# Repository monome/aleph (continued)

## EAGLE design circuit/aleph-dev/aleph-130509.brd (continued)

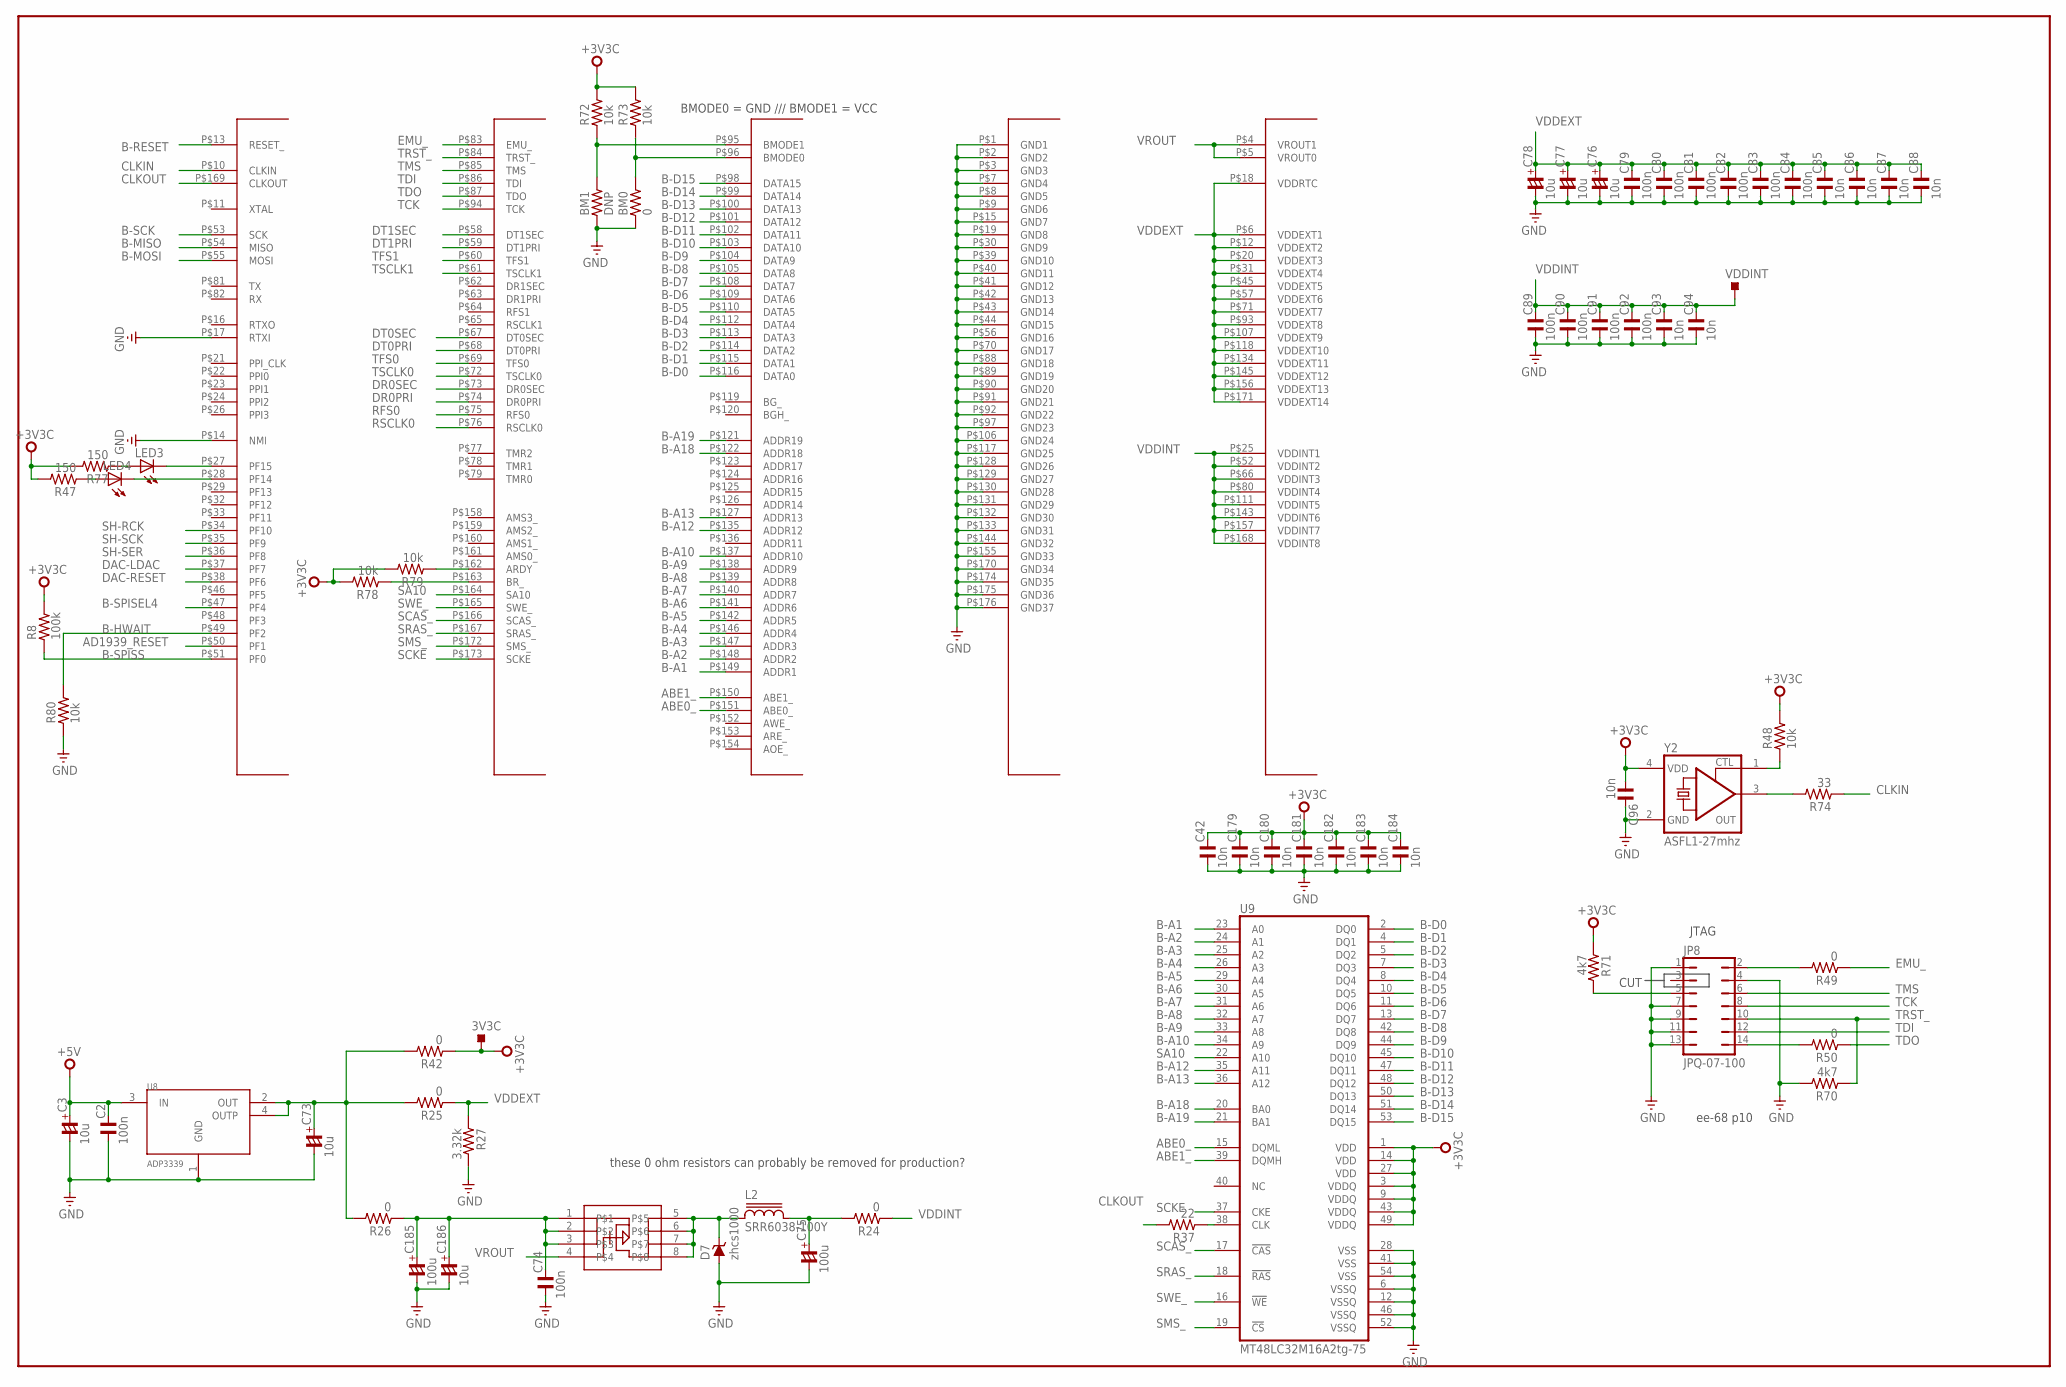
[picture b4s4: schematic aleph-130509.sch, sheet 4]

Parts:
3V3C: TPS-SMD-15R; SMD-15R
BM0: 0; R0603
BM1: DNP; R0603
C2, C74: 100n; C1206
C3, C73, C76, C77, C78, C186: 10u; C1206/T
C42, C85, C86, C87, C88, C93, C94, C96, C179, C180, C181, C182, C183, C184: 10n; C0603
C75, C185: 100u; C1210/T
C79, C80, C81, C82, C83, C84, C89, C90, C91, C92: 100n; C0603
D7: zhcs1000; SOT23
DSP1: BF533; LQFP176
JP8: JPQ-07-100; JPQ-07
L2: SRR6038-100Y; SRR6038
LED3, LED4: LEDCHIPLED_0805; CHIPLED_0805
R8: 100k; R0603
R24, R25, R26, R42, R49, R50: 0; R0603
R27: 3.32k; R0603
R37: 22; R0603
R47, R77: 150; R0603
R48, R72, R73, R78, R79, R80: 10k; R0603
R70, R71: 4k7; R0603
R74: 33; R0603
U8: ADP3339; SOT223
U9: MT48LC32M16A2tg-75; TSOP54
U18: FDS9431A; SO08
VDDINT: TPS-SMD-10R; SMD-10R
Y2: ASFL1-27mhz; ASFL1

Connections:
+3V3C: 3V3C.TP, C42.2, C96.1, C179.2, C180.2, C181.2, C182.2, C183.2, C184.2, R8.2, R42.1, R47.2, R48.2, R71.1, R72.2, R73.2, R77.2, R78.2, R79.2, U9.1 (VDD), U9.3 (VDDQ), U9.9 (VDDQ), U9.14 (VDD), U9.27 (VDD), U9.43 (VDDQ), U9.49 (VDDQ), Y2.4 (VDD); also elsewhere on the board
+5V: C2.2, C3.+, U8.3 (IN); also elsewhere on the board
ABE0_: DSP1.P$151 (ABE0_), U9.15 (DQML)
ABE1_: DSP1.P$150 (ABE1_), U9.39 (DQMH)
AD1939_RESET: DSP1.P$50 (PF1); also elsewhere on the board
B-A1: DSP1.P$149 (ADDR1), U9.23 (A0)
B-A2: DSP1.P$148 (ADDR2), U9.24 (A1)
B-A3: DSP1.P$147 (ADDR3), U9.25 (A2)
B-A4: DSP1.P$146 (ADDR4), U9.26 (A3)
B-A5: DSP1.P$142 (ADDR5), U9.29 (A4)
B-A6: DSP1.P$141 (ADDR6), U9.30 (A5)
B-A7: DSP1.P$140 (ADDR7), U9.31 (A6)
B-A8: DSP1.P$139 (ADDR8), U9.32 (A7)
B-A9: DSP1.P$138 (ADDR9), U9.33 (A8)
B-A10: DSP1.P$137 (ADDR10), U9.34 (A9)
B-A12: DSP1.P$135 (ADDR12), U9.35 (A11)
B-A13: DSP1.P$127 (ADDR13), U9.36 (A12)
B-A18: DSP1.P$122 (ADDR18), U9.20 (BA0)
B-A19: DSP1.P$121 (ADDR19), U9.21 (BA1)
B-D0: DSP1.P$116 (DATA0), U9.2 (DQ0)
B-D1: DSP1.P$115 (DATA1), U9.4 (DQ1)
B-D2: DSP1.P$114 (DATA2), U9.5 (DQ2)
B-D3: DSP1.P$113 (DATA3), U9.7 (DQ3)
B-D4: DSP1.P$112 (DATA4), U9.8 (DQ4)
B-D5: DSP1.P$110 (DATA5), U9.10 (DQ5)
B-D6: DSP1.P$109 (DATA6), U9.11 (DQ6)
B-D7: DSP1.P$108 (DATA7), U9.13 (DQ7)
B-D8: DSP1.P$105 (DATA8), U9.42 (DQ8)
B-D9: DSP1.P$104 (DATA9), U9.44 (DQ9)
B-D10: DSP1.P$103 (DATA10), U9.45 (DQ10)
B-D11: DSP1.P$102 (DATA11), U9.47 (DQ11)
B-D12: DSP1.P$101 (DATA12), U9.48 (DQ12)
B-D13: DSP1.P$100 (DATA13), U9.50 (DQ13)
B-D14: DSP1.P$99 (DATA14), U9.51 (DQ14)
B-D15: DSP1.P$98 (DATA15), U9.53 (DQ15)
B-HWAIT: DSP1.P$49 (PF2), R80.2; also elsewhere on the board
B-MISO: DSP1.P$54 (MISO); also elsewhere on the board
B-MOSI: DSP1.P$55 (MOSI); also elsewhere on the board
B-RESET: DSP1.P$13 (RESET_); also elsewhere on the board
B-SCK: DSP1.P$53 (SCK); also elsewhere on the board
B-SPISEL4: DSP1.P$47 (PF4)
B-SPISS: DSP1.P$51 (PF0), R8.1; also elsewhere on the board
BMODE0: BM0.2, DSP1.P$96 (BMODE0), R73.1
BMODE1: BM1.2, DSP1.P$95 (BMODE1), R72.1
CLKIN: DSP1.P$10 (CLKIN), R74.1
CLKOUT: DSP1.P$169 (CLKOUT), R37.2
DAC-LDAC: DSP1.P$37 (PF7); also elsewhere on the board
DAC-RESET: DSP1.P$38 (PF6); also elsewhere on the board
DR0PRI: DSP1.P$74 (DR0PRI); also elsewhere on the board
DR0SEC: DSP1.P$73 (DR0SEC); also elsewhere on the board
DT0PRI: DSP1.P$68 (DT0PRI); also elsewhere on the board
DT0SEC: DSP1.P$67 (DT0SEC); also elsewhere on the board
DT1PRI: DSP1.P$59 (DT1PRI)
DT1SEC: DSP1.P$58 (DT1SEC); also elsewhere on the board
EMU_: DSP1.P$83 (EMU_), R49.1
GND: BM0.1, BM1.1, C2.1, C3.-, C42.1, C73.-, C74.1, C75.-, C76.-, C77.-, C78.-, C79.1, C80.1, C81.1, C82.1, C83.1, C84.1, C85.1, C86.1, C87.1, C88.1, C89.1, C90.1, C91.1, C92.1, C93.1, C94.1, C96.2, C179.1, C180.1, C181.1, C182.1, C183.1, C184.1, C185.-, C186.-, D7.1 (A), DSP1.P$1 (GND1), DSP1.P$2 (GND2), DSP1.P$3 (GND3), DSP1.P$7 (GND4), DSP1.P$8 (GND5), DSP1.P$9 (GND6), DSP1.P$14 (NMI), DSP1.P$15 (GND7), DSP1.P$17 (RTXI), DSP1.P$19 (GND8), DSP1.P$30 (GND9), DSP1.P$39 (GND10), DSP1.P$40 (GND11), DSP1.P$41 (GND12), DSP1.P$42 (GND13), DSP1.P$43 (GND14), DSP1.P$44 (GND15), DSP1.P$56 (GND16), DSP1.P$70 (GND17), DSP1.P$88 (GND18), DSP1.P$89 (GND19), DSP1.P$90 (GND20), DSP1.P$91 (GND21), DSP1.P$92 (GND22), DSP1.P$97 (GND23), DSP1.P$106 (GND24), DSP1.P$117 (GND25), DSP1.P$128 (GND26), DSP1.P$129 (GND27), DSP1.P$130 (GND28), DSP1.P$131 (GND29), DSP1.P$132 (GND30), DSP1.P$133 (GND31), DSP1.P$144 (GND32), DSP1.P$155 (GND33), DSP1.P$170 (GND34), DSP1.P$174 (GND35), DSP1.P$175 (GND36), DSP1.P$176 (GND37), JP8.1, JP8.4, JP8.7, JP8.9, JP8.11, JP8.13, R27.2, R70.2, R80.1, U8.1 (GND), U9.6 (VSSQ), U9.12 (VSSQ), U9.28 (VSS), U9.41 (VSS), U9.46 (VSSQ), U9.52 (VSSQ), U9.54 (VSS), Y2.2 (GND); also elsewhere on the board
unnamed: C73.+, R25.2, R26.2, R42.2, U8.2 (OUT), U8.4 (OUTP)
unnamed: C74.2, C185.+, C186.+, R26.1, U18.1, U18.2, U18.3
unnamed: D7.3 (C), L2.1, U18.5, U18.6, U18.7, U18.8
unnamed: C75.+, L2.2, R24.2
unnamed: R37.1, U9.38 (CLK)
unnamed: R48.1, Y2.1 (CTL)
unnamed: JP8.2, R49.2
unnamed: JP8.5, R71.2
unnamed: DSP1.P$163 (BR_), R78.1
unnamed: JP8.14, R50.2
unnamed: DSP1.P$162 (ARDY), R79.1
unnamed: R74.2, Y2.3 (OUT)
unnamed: DSP1.P$27 (PF15), LED3.C
unnamed: DSP1.P$28 (PF14), LED4.C
unnamed: LED3.A, R77.1
unnamed: LED4.A, R47.1
RFS0: DSP1.P$75 (RFS0); also elsewhere on the board
RSCLK0: DSP1.P$76 (RSCLK0); also elsewhere on the board
SA10: DSP1.P$164 (SA10), U9.22 (A10)
SCAS_: DSP1.P$166 (SCAS_), U9.17 (!CAS!)
SCKE: DSP1.P$173 (SCKE), U9.37 (CKE)
SH-RCK: DSP1.P$34 (PF10)
SH-SCK: DSP1.P$35 (PF9)
SH-SER: DSP1.P$36 (PF8)
SMS_: DSP1.P$172 (SMS_), U9.19 (!CS!)
SRAS_: DSP1.P$167 (SRAS_), U9.18 (!RAS!)
SWE_: DSP1.P$165 (SWE_), U9.16 (!WE!)
TCK: DSP1.P$94 (TCK), JP8.8
TDI: DSP1.P$86 (TDI), JP8.12
TDO: DSP1.P$87 (TDO), R50.1
TFS0: DSP1.P$69 (TFS0); also elsewhere on the board
TFS1: DSP1.P$60 (TFS1); also elsewhere on the board
TMS: DSP1.P$85 (TMS), JP8.6
TRST_: DSP1.P$84 (TRST_), JP8.10, R70.1
TSCLK0: DSP1.P$72 (TSCLK0); also elsewhere on the board
TSCLK1: DSP1.P$61 (TSCLK1); also elsewhere on the board
VDDEXT: C76.+, C77.+, C78.+, C79.2, C80.2, C81.2, C82.2, C83.2, C84.2, C85.2, C86.2, C87.2, C88.2, DSP1.P$6 (VDDEXT1), DSP1.P$12 (VDDEXT2), DSP1.P$18 (VDDRTC), DSP1.P$20 (VDDEXT3), DSP1.P$31 (VDDEXT4), DSP1.P$45 (VDDEXT5), DSP1.P$57 (VDDEXT6), DSP1.P$71 (VDDEXT7), DSP1.P$93 (VDDEXT8), DSP1.P$107 (VDDEXT9), DSP1.P$118 (VDDEXT10), DSP1.P$134 (VDDEXT11), DSP1.P$145 (VDDEXT12), DSP1.P$156 (VDDEXT13), DSP1.P$171 (VDDEXT14), R25.1, R27.1
VDDINT: C89.2, C90.2, C91.2, C92.2, C93.2, C94.2, DSP1.P$25 (VDDINT1), DSP1.P$52 (VDDINT2), DSP1.P$66 (VDDINT3), DSP1.P$80 (VDDINT4), DSP1.P$111 (VDDINT5), DSP1.P$143 (VDDINT6), DSP1.P$157 (VDDINT7), DSP1.P$168 (VDDINT8), R24.1, VDDINT.TP
VROUT: DSP1.P$4 (VROUT1), DSP1.P$5 (VROUT0), U18.4

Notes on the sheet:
these 0 ohm resistors can probably be removed for production?
ee-68 p10
CUT
JTAG
BMODE0 = GND /// BMODE1 = VCC

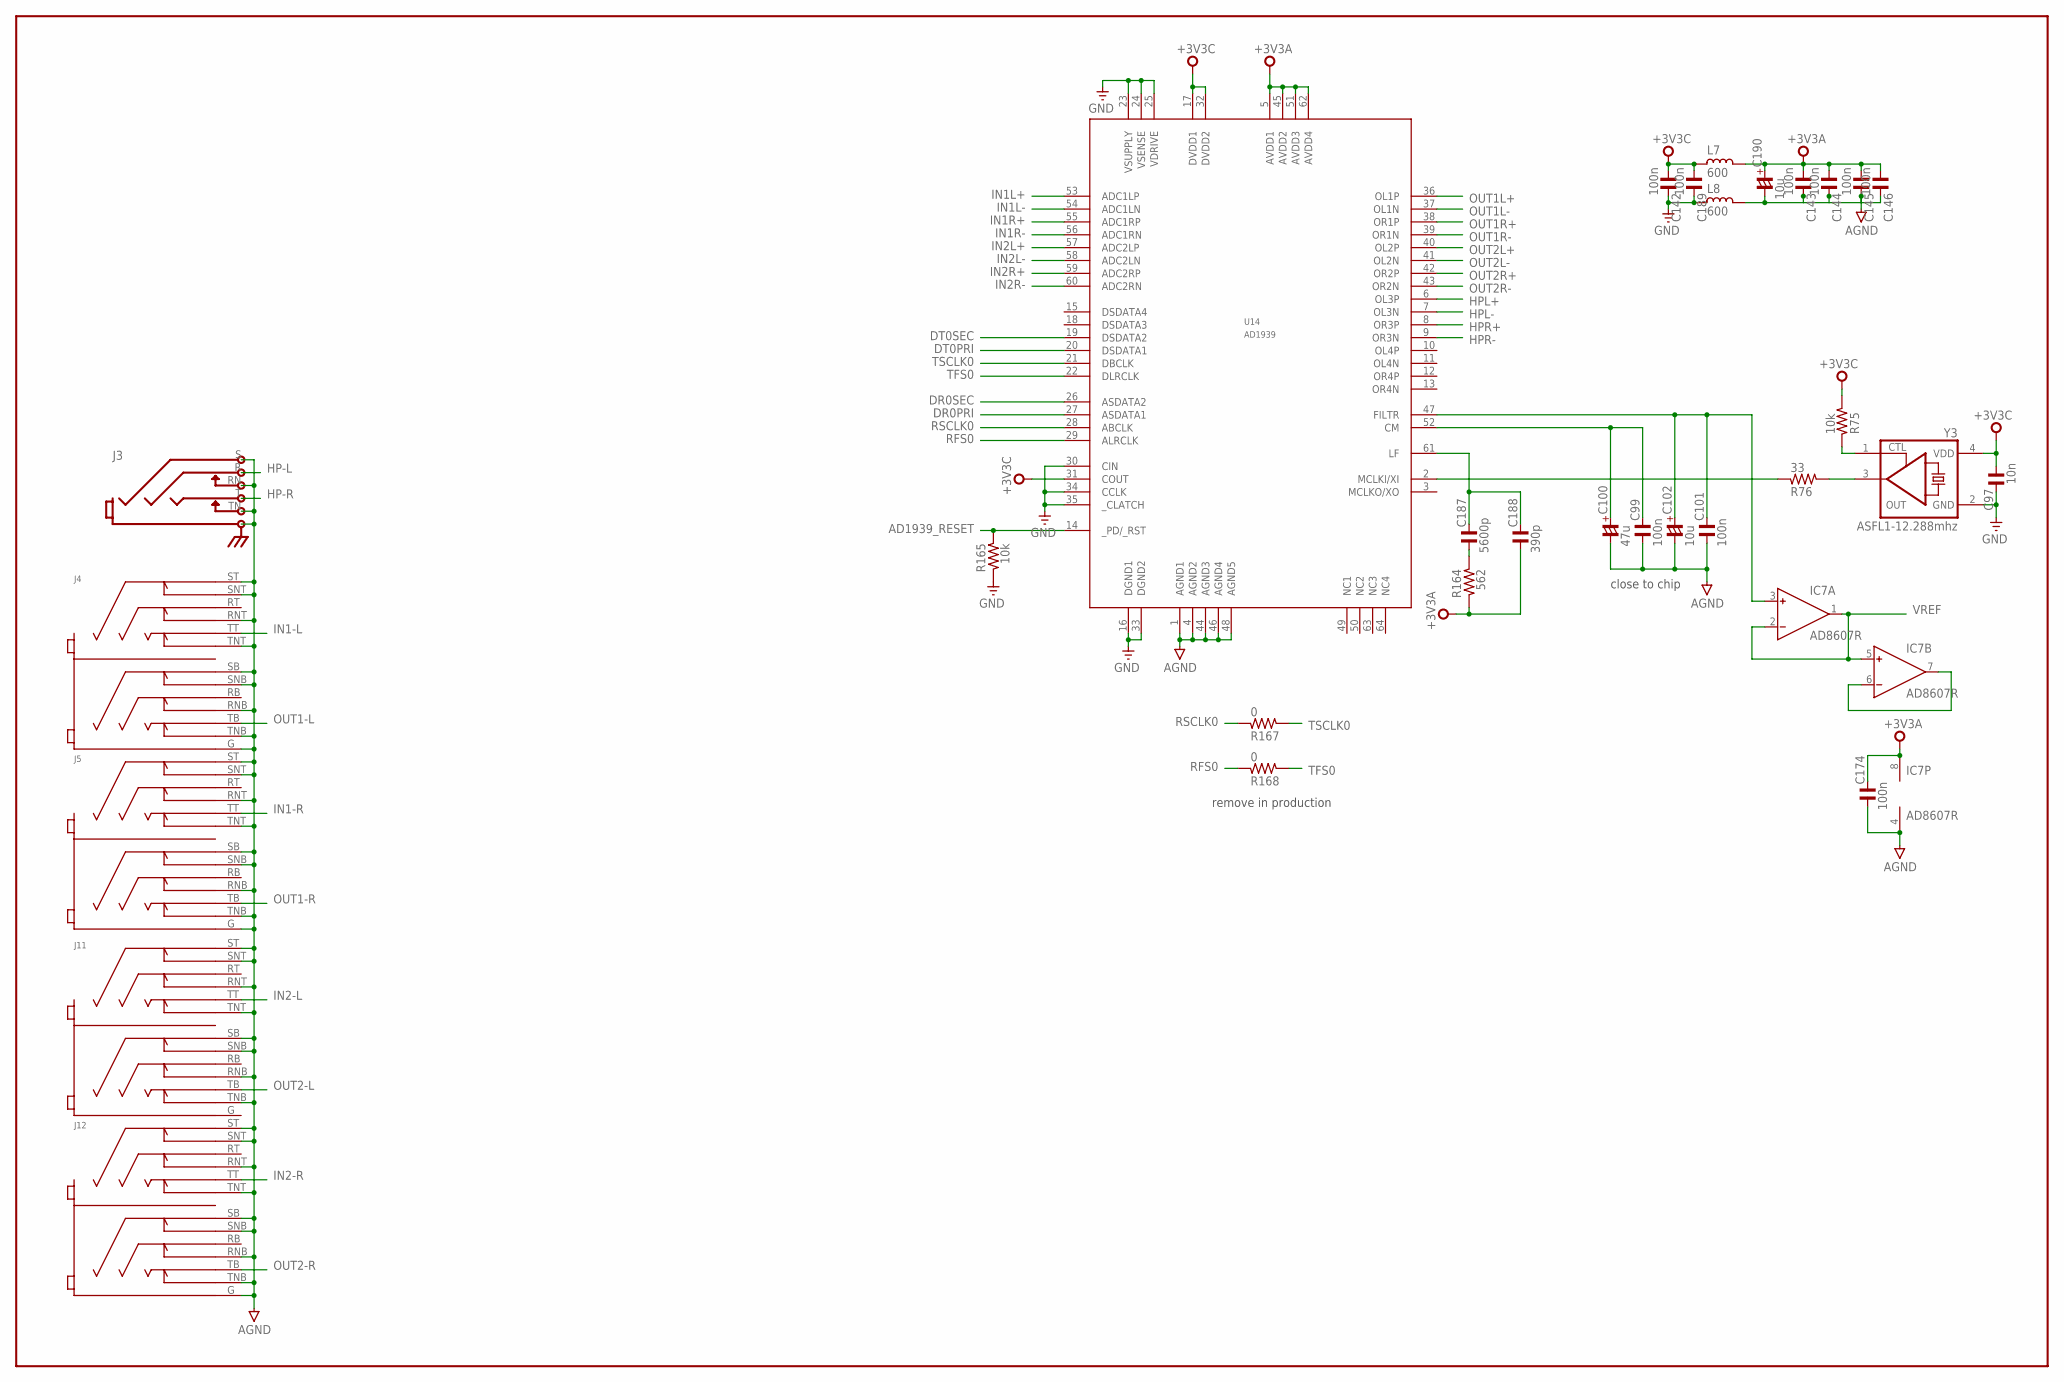
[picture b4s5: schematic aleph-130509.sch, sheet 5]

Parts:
C97: 10n; C0603
C99, C101, C142, C143, C144, C145, C146, C174, C189: 100n; C0603
C100: 47u; C1206/T
C102, C190: 10u; C1206/T
C187: 5600p; C0603
C188: 390p; C0603
IC7: AD8607R; SO8
J3: STEREOSW2GND; NEUTRIK-NRJ6HM-1
J4, J5, J11, J12: NSJ12HF
L7, L8: 600; L1206
R75, R165: 10k; R0603
R76: 33; R0603
R164: 562; R0603
R167, R168: 0; R0603
U14: AD1939; SQFP-S-10X10-64
Y3: ASFL1-12.288mhz; ASFL1

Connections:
+3V3A: C143.1, C144.1, C145.1, C146.1, C174.2, C188.1, C190.+, IC7.8 (V+), L7.1, R164.2, U14.5 (AVDD1), U14.45 (AVDD2), U14.51 (AVDD3), U14.62 (AVDD4); also elsewhere on the board
+3V3C: C97.1, C142.1, C189.1, L7.2, R75.2, U14.17 (DVDD1), U14.31 (COUT), U14.32 (DVDD2), Y3.4 (VDD); also elsewhere on the board
AD1939_RESET: R165.1, U14.14 (_PD/_RST); also elsewhere on the board
AGND: C99.1, C100.-, C101.1, C102.-, C143.2, C144.2, C145.2, C146.2, C174.1, C190.-, IC7.4 (V-), J3.RN, J3.S, J3.TN, J4.G, J4.RNB, J4.RNT, J4.SB, J4.SNB, J4.SNT, J4.ST, J4.TNB, J4.TNT, J5.G, J5.RNB, J5.RNT, J5.SB, J5.SNB, J5.SNT, J5.ST, J5.TNB, J5.TNT, J11.RNB, J11.RNT, J11.SB, J11.SNB, J11.SNT, J11.ST, J11.TNB, J11.TNT, J12.G, J12.RNB, J12.RNT, J12.SB, J12.SNB, J12.SNT, J12.ST, J12.TNB, J12.TNT, L8.1, U14.1 (AGND1), U14.4 (AGND2), U14.44 (AGND3), U14.46 (AGND4), U14.48 (AGND5); also elsewhere on the board
DR0PRI: U14.27 (ASDATA1); also elsewhere on the board
DR0SEC: U14.26 (ASDATA2); also elsewhere on the board
DT0PRI: U14.20 (DSDATA1); also elsewhere on the board
DT0SEC: U14.19 (DSDATA2); also elsewhere on the board
GND: C97.2, C142.2, C189.2, L8.2, R165.2, U14.16 (DGND1), U14.23 (VSUPPLY), U14.24 (VSENSE), U14.25 (VDRIVE), U14.30 (CIN), U14.33 (DGND2), U14.34 (CCLK), U14.35 (_CLATCH), Y3.2 (GND); also elsewhere on the board
HP-L: J3.R; also elsewhere on the board
HP-R: J3.T; also elsewhere on the board
HPL+: U14.6 (OL3P)
HPL-: U14.7 (OL3N)
HPR+: U14.8 (OR3P)
HPR-: U14.9 (OR3N)
IN1-L: J4.TT; also elsewhere on the board
IN1-R: J5.TT; also elsewhere on the board
IN1L+: U14.53 (ADC1LP); also elsewhere on the board
IN1L-: U14.54 (ADC1LN); also elsewhere on the board
IN1R+: U14.55 (ADC1RP); also elsewhere on the board
IN1R-: U14.56 (ADC1RN); also elsewhere on the board
IN2-L: J11.TT; also elsewhere on the board
IN2-R: J12.TT; also elsewhere on the board
IN2L+: U14.57 (ADC2LP); also elsewhere on the board
IN2L-: U14.58 (ADC2LN); also elsewhere on the board
IN2R+: U14.59 (ADC2RP); also elsewhere on the board
IN2R-: U14.60 (ADC2RN); also elsewhere on the board
unnamed: R75.1, Y3.1 (CTL)
unnamed: R76.2, Y3.3 (OUT)
unnamed: R76.1, U14.2 (MCLKI/XI)
unnamed: C101.2, C102.+, IC7.3 (IN+), U14.47 (FILTR)
unnamed: C99.2, C100.+, U14.52 (CM)
unnamed: C187.2, C188.2, U14.61 (LF)
unnamed: C187.1, R164.1
unnamed: IC7.6 (IN-), IC7.7 (OUT)
OUT1-L: J4.TB; also elsewhere on the board
OUT1-R: J5.TB; also elsewhere on the board
OUT1L+: U14.36 (OL1P); also elsewhere on the board
OUT1L-: U14.37 (OL1N); also elsewhere on the board
OUT1R+: U14.38 (OR1P); also elsewhere on the board
OUT1R-: U14.39 (OR1N); also elsewhere on the board
OUT2-L: J11.TB; also elsewhere on the board
OUT2-R: J12.TB; also elsewhere on the board
OUT2L+: U14.40 (OL2P); also elsewhere on the board
OUT2L-: U14.41 (OL2N); also elsewhere on the board
OUT2R+: U14.42 (OR2P); also elsewhere on the board
OUT2R-: U14.43 (OR2N); also elsewhere on the board
RFS0: R168.1, U14.29 (ALRCLK); also elsewhere on the board
RSCLK0: R167.1, U14.28 (ABCLK); also elsewhere on the board
TFS0: R168.2, U14.22 (DLRCLK); also elsewhere on the board
TSCLK0: R167.2, U14.21 (DBCLK); also elsewhere on the board
VREF: IC7.1 (OUT), IC7.2 (IN-), IC7.5 (IN+); also elsewhere on the board

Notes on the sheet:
close to chip
remove in production

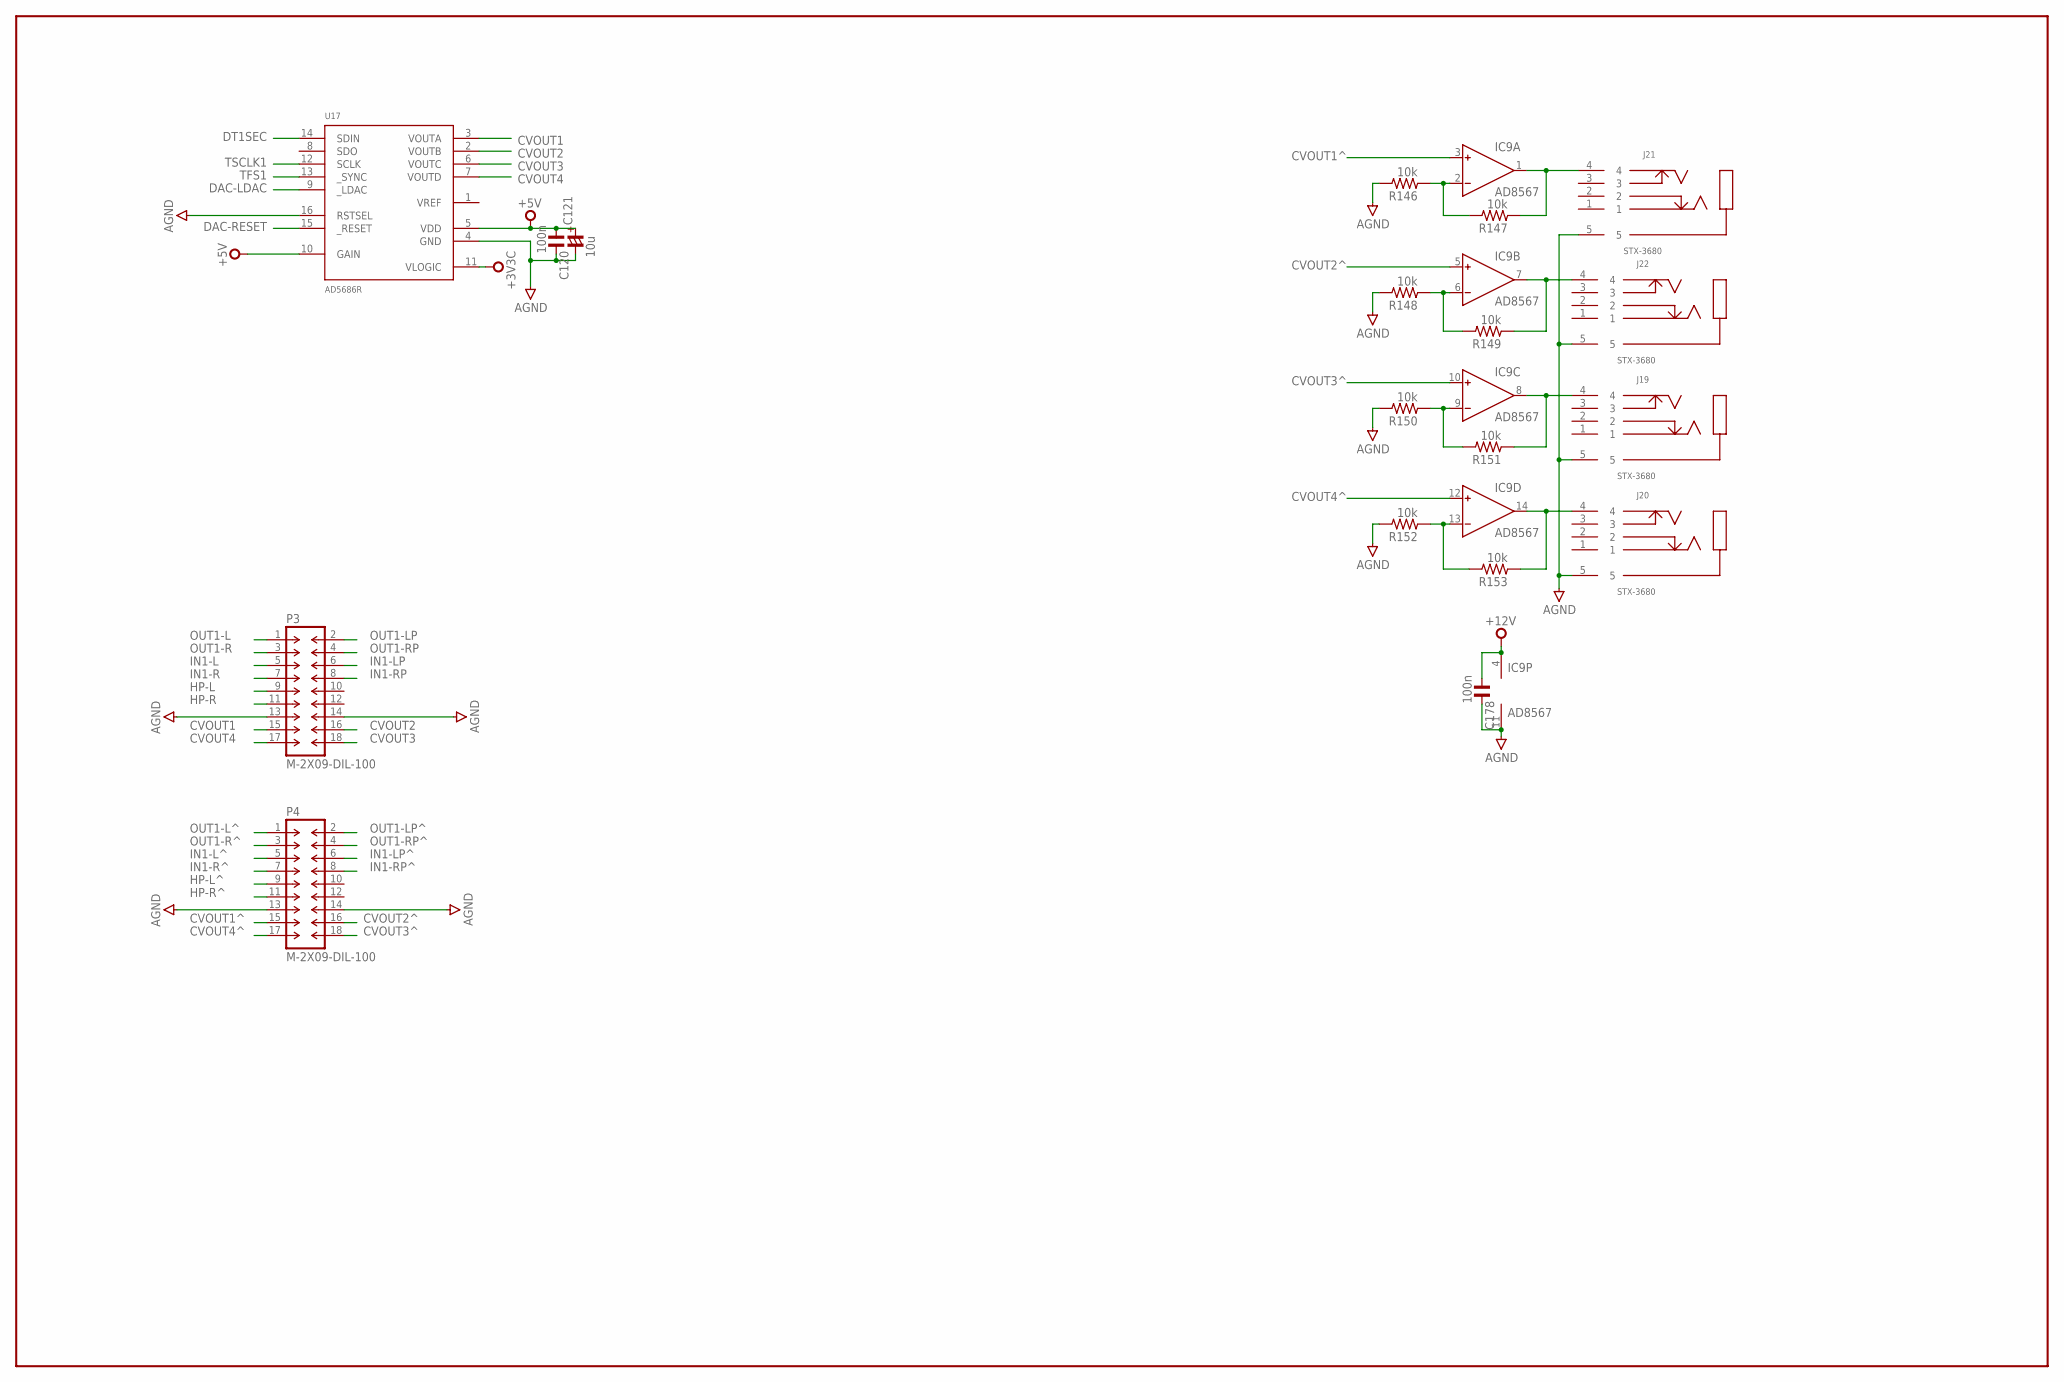
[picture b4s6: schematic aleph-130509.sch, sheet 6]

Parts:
C120, C178: 100n; C0603
C121: 10u; C1206/T
IC9: AD8567; TSSOP14
J19, J20, J21, J22: STX-3680
P3, P4: M-2X09-DIL-100; DIL-100-2X09
R146, R147, R148, R149, R150, R151, R152, R153: 10k; R0603
U17: AD5686R; TSSOP16

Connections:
+3V3C: U17.11 (VLOGIC); also elsewhere on the board
+5V: C120.1, C121.+, U17.5 (VDD), U17.10 (GAIN); also elsewhere on the board
+12V: C178.1, IC9.4 (V+); also elsewhere on the board
AGND: C120.2, C121.-, C178.2, IC9.11 (V-), J19.5, J20.5, J21.5, J22.5, P3.13, P3.14, P4.13, P4.14, R146.2, R148.2, R150.2, R152.2, U17.4 (GND), U17.16 (RSTSEL); also elsewhere on the board
CVOUT1: P3.15, U17.3 (VOUTA)
CVOUT1^: IC9.3 (IN+), P4.15
CVOUT2: P3.16, U17.2 (VOUTB)
CVOUT2^: IC9.5 (IN+), P4.16
CVOUT3: P3.18, U17.6 (VOUTC)
CVOUT3^: IC9.10 (IN+), P4.18
CVOUT4: P3.17, U17.7 (VOUTD)
CVOUT4^: IC9.12 (IN+), P4.17
DAC-LDAC: U17.9 (_LDAC); also elsewhere on the board
DAC-RESET: U17.15 (_RESET); also elsewhere on the board
DT1SEC: U17.14 (SDIN); also elsewhere on the board
HP-L: P3.9; also elsewhere on the board
HP-L^: P4.9; also elsewhere on the board
HP-R: P3.11; also elsewhere on the board
HP-R^: P4.11; also elsewhere on the board
IN1-L: P3.5; also elsewhere on the board
IN1-LP: P3.6; also elsewhere on the board
IN1-LP^: P4.6; also elsewhere on the board
IN1-L^: P4.5; also elsewhere on the board
IN1-R: P3.7; also elsewhere on the board
IN1-RP: P3.8; also elsewhere on the board
IN1-RP^: P4.8; also elsewhere on the board
IN1-R^: P4.7; also elsewhere on the board
unnamed: IC9.2 (IN-), R146.1, R147.2
unnamed: IC9.1 (OUT), J21.4, R147.1
unnamed: IC9.6 (IN-), R148.1, R149.2
unnamed: IC9.9 (IN-), R150.1, R151.2
unnamed: IC9.13 (IN-), R152.1, R153.2
unnamed: IC9.8 (OUT), J19.4, R151.1
unnamed: IC9.14 (OUT), J20.4, R153.1
unnamed: IC9.7 (OUT), J22.4, R149.1
OUT1-L: P3.1; also elsewhere on the board
OUT1-LP: P3.2; also elsewhere on the board
OUT1-LP^: P4.2; also elsewhere on the board
OUT1-L^: P4.1; also elsewhere on the board
OUT1-R: P3.3; also elsewhere on the board
OUT1-RP: P3.4; also elsewhere on the board
OUT1-RP^: P4.4; also elsewhere on the board
OUT1-R^: P4.3; also elsewhere on the board
TFS1: U17.13 (_SYNC); also elsewhere on the board
TSCLK1: U17.12 (SCLK); also elsewhere on the board

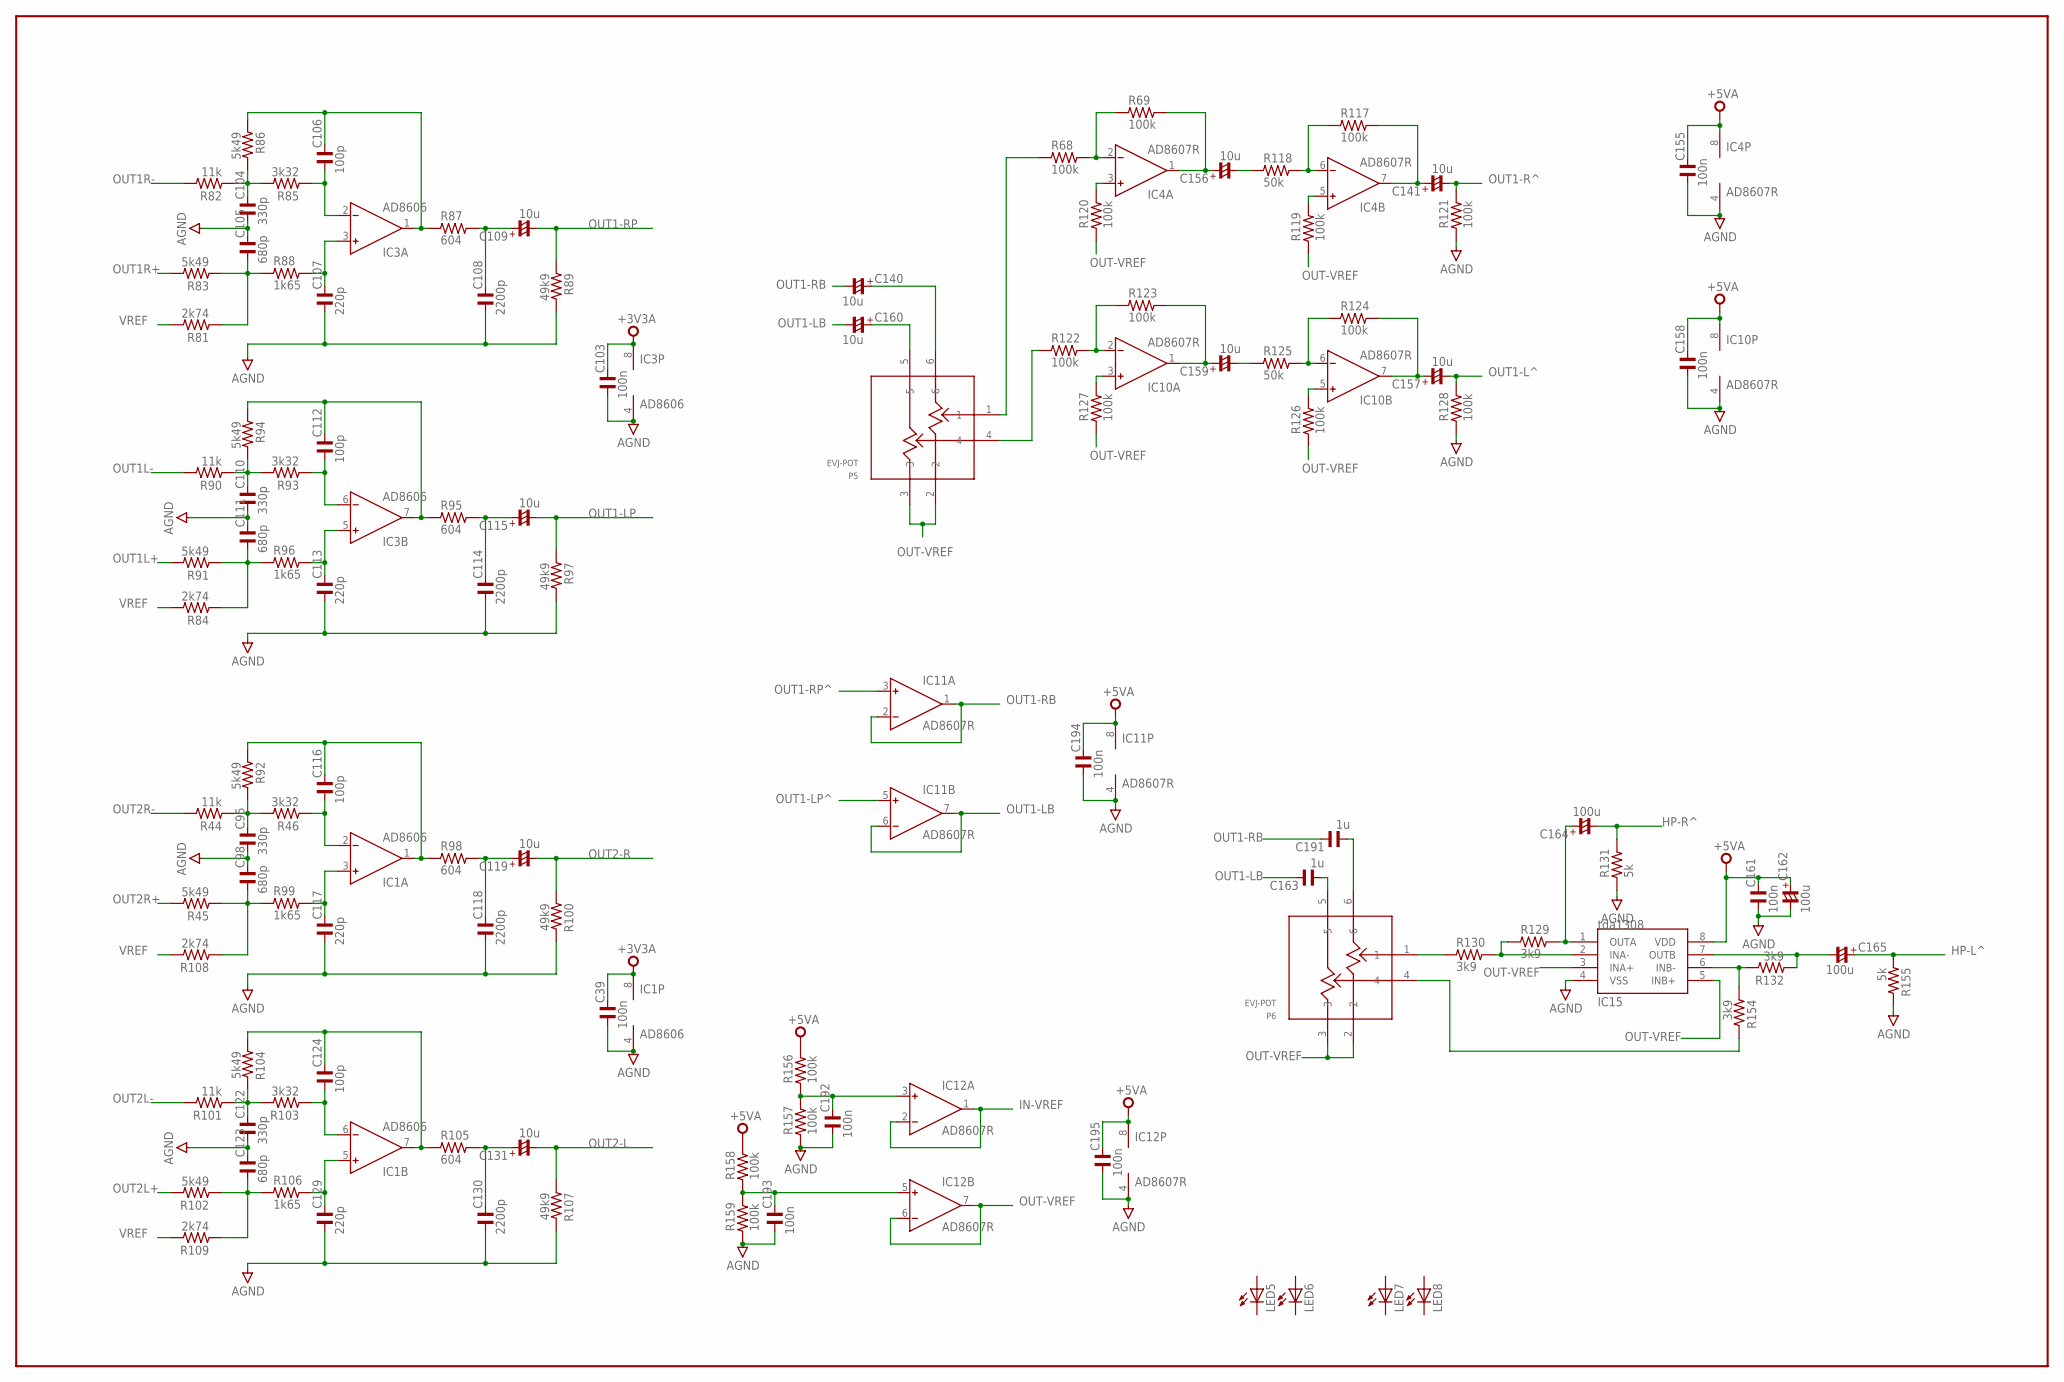
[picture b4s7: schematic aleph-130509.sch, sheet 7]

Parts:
C39, C103, C155, C158, C161, C192, C193, C194, C195: 100n; C0603
C95, C104, C110, C122: 330p; C0603
C98, C105, C111, C123: 680p; C0603
C106, C112, C116, C124: 100p; C0603
C107, C113, C117, C129: 220p; C0603
C108, C114, C118, C130: 2200p; C0603
C109, C115, C119, C131, C140, C141, C156, C157, C159, C160: 10u; C1206/T
C162, C164, C165: 100u; C1206/T
C163, C191: 1u; C0603
IC1, IC3: AD8606; SO8
IC4, IC10, IC11, IC12: AD8607R; SO8
IC15: tda1308; SO08
LED5, LED6, LED7, LED8: LEDCHIPLED_0805; CHIPLED_0805
P5, P6: EVJ-POT
R44, R82, R90, R101: 11k; R0603
R45, R83, R86, R91, R92, R94, R102, R104: 5k49; R0603
R46, R85, R93, R103: 3k32; R0603
R68, R69, R117, R119, R120, R121, R122, R123, R124, R126, R127, R128, R156, R157, R158, R159: 100k; R0603
R81, R84, R108, R109: 2k74; R0603
R87, R95, R98, R105: 604; R0603
R88, R96, R99, R106: 1k65; R0603
R89, R97, R100, R107: 49k9; R0603
R118, R125: 50k; R0603
R129, R130, R132, R154: 3k9; R0603
R131, R155: 5k; R0603

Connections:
+3V3A: C39.2, C103.2, IC1.8 (V+), IC3.8 (V+); also elsewhere on the board
+5VA: C155.2, C158.2, C161.2, C162.+, C194.2, C195.2, IC4.8 (V+), IC10.8 (V+), IC11.8 (V+), IC12.8 (V+), IC15.8 (VDD), R156.2, R158.2; also elsewhere on the board
AGND: C39.1, C95.1, C98.2, C103.1, C104.1, C105.2, C107.1, C108.1, C110.1, C111.2, C113.1, C114.1, C117.1, C118.1, C122.1, C123.2, C129.1, C130.1, C155.1, C158.1, C161.1, C162.-, C192.1, C193.1, C194.1, C195.1, IC1.4 (V-), IC3.4 (V-), IC4.4 (V-), IC10.4 (V-), IC11.4 (V-), IC12.4 (V-), IC15.4 (VSS), R89.2, R97.2, R100.2, R107.2, R121.1, R128.1, R131.1, R155.2, R157.1, R159.1; also elsewhere on the board
HP-L^: C165.+, R155.1; also elsewhere on the board
HP-R^: C164.-, R131.2; also elsewhere on the board
IN-VREF: IC12.1 (OUT), IC12.2 (IN-); also elsewhere on the board
unnamed: C104.2, R82.1, R85.2, R86.2
unnamed: C105.1, R81.1, R83.1, R88.1
unnamed: C107.2, IC3.3 (IN+), R88.2
unnamed: C106.2, IC3.1 (OUT), R86.1, R87.1
unnamed: C108.2, C109.+, R87.2
unnamed: C110.2, R90.1, R93.2, R94.2
unnamed: C106.1, IC3.2 (IN-), R85.1
unnamed: C111.1, R84.1, R91.1, R96.1
unnamed: C113.2, IC3.5 (IN+), R96.2
unnamed: C112.2, IC3.7 (OUT), R94.1, R95.1
unnamed: C114.2, C115.+, R95.2
unnamed: C112.1, IC3.6 (IN-), R93.1
unnamed: C95.2, R44.1, R46.2, R92.2
unnamed: C98.1, R45.1, R99.1, R108.1
unnamed: C117.2, IC1.3 (IN+), R99.2
unnamed: C116.2, IC1.1 (OUT), R92.1, R98.1
unnamed: C118.2, C119.+, R98.2
unnamed: C116.1, IC1.2 (IN-), R46.1
unnamed: C122.2, R101.1, R103.2, R104.2
unnamed: C123.1, R102.1, R106.1, R109.1
unnamed: C129.2, IC1.5 (IN+), R106.2
unnamed: IC4.3 (IN+), R120.2
unnamed: IC4.2 (IN-), R68.2, R69.1
unnamed: C140.+, P5.6
unnamed: C124.2, IC1.7 (OUT), R104.1, R105.1
unnamed: C156.+, IC4.1 (OUT), R69.2
unnamed: C130.2, C131.+, R105.2
unnamed: C124.1, IC1.6 (IN-), R103.1
unnamed: C156.-, R118.1
unnamed: IC4.6 (IN-), R117.1, R118.2
unnamed: C141.+, IC4.7 (OUT), R117.2
unnamed: IC10.3 (IN+), R127.2
unnamed: IC4.5 (IN+), R119.2
unnamed: P5.1, R68.1
unnamed: IC10.2 (IN-), R122.2, R123.1
unnamed: C159.+, IC10.1 (OUT), R123.2
unnamed: C159.-, R125.1
unnamed: IC10.6 (IN-), R124.1, R125.2
unnamed: C157.+, IC10.7 (OUT), R124.2
unnamed: IC10.5 (IN+), R126.2
unnamed: P5.4, R122.1
unnamed: C160.+, P5.5
unnamed: IC15.2 (INA-), R129.1, R130.2
unnamed: C164.+, IC15.1 (OUTA), R129.2
unnamed: C163.1, P6.5
unnamed: IC15.6 (INB-), R132.2, R154.1
unnamed: C191.1, P6.6
unnamed: C192.2, IC12.3 (IN+), R156.1, R157.2
unnamed: C165.-, IC15.7 (OUTB), R132.1
unnamed: P6.4, R154.2
unnamed: P6.1, R130.1
unnamed: C193.2, IC12.5 (IN+), R158.1, R159.2
OUT1-LB: C160.-, C163.2, IC11.6 (IN-), IC11.7 (OUT)
OUT1-LP: C115.-, R97.1; also elsewhere on the board
OUT1-LP^: IC11.5 (IN+); also elsewhere on the board
OUT1-L^: C157.-, R128.2; also elsewhere on the board
OUT1-RB: C140.-, C191.2, IC11.1 (OUT), IC11.2 (IN-)
OUT1-RP: C109.-, R89.1; also elsewhere on the board
OUT1-RP^: IC11.3 (IN+); also elsewhere on the board
OUT1-R^: C141.-, R121.2; also elsewhere on the board
OUT1L+: R91.2; also elsewhere on the board
OUT1L-: R90.2; also elsewhere on the board
OUT1R+: R83.2; also elsewhere on the board
OUT1R-: R82.2; also elsewhere on the board
OUT2-L: C131.-, R107.1; also elsewhere on the board
OUT2-R: C119.-, R100.1; also elsewhere on the board
OUT2L+: R102.2; also elsewhere on the board
OUT2L-: R101.2; also elsewhere on the board
OUT2R+: R45.2; also elsewhere on the board
OUT2R-: R44.2; also elsewhere on the board
OUT-VREF: IC12.6 (IN-), IC12.7 (OUT), IC15.3 (INA+), IC15.5 (INB+), P5.2, P5.3, P6.2, P6.3, R119.1, R120.1, R126.1, R127.1
VREF: R81.2, R84.2, R108.2, R109.2; also elsewhere on the board
